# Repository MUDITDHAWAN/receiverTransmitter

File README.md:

# receiverTransmitter

Components Type Purpose
    HC-49U Crystal Oscillator: Generate 2MHz signal
    CD4017BE Frequency Divider:  Convert 2MHz signal to 40KHz signal
    CD4049 Buffer Amplifier:  Allows for impedance transformation and protects
        circuits from fluctuations in currents.
    MCUSD16A40S12R0 Piezoelectric Transducer: Convert electrical to ultrasonic signal and back
        (Transmitter and Receiver)
    MC33079 Low Noise Amplifier: Amplify received signal without introducing too much
        noise

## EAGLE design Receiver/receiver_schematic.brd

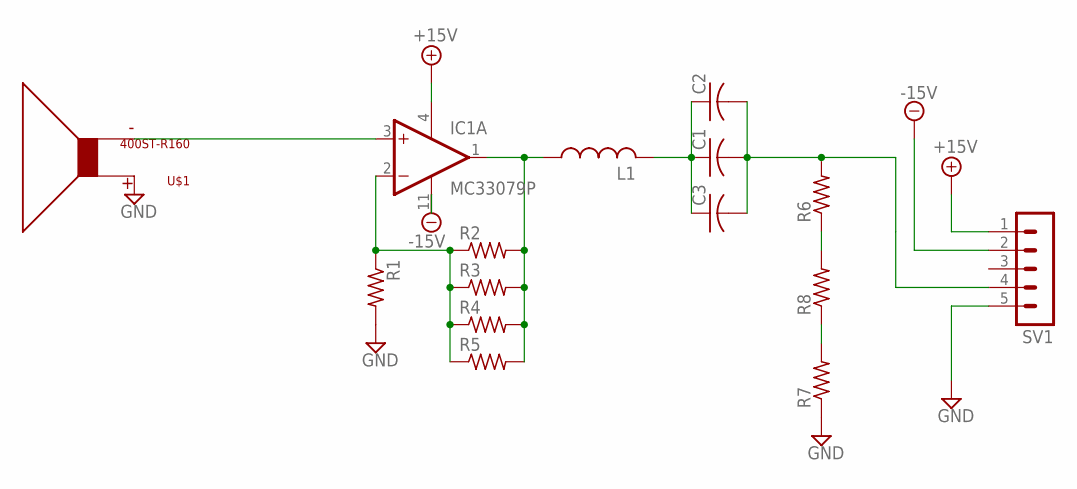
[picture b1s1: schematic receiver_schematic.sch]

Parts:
C1, C2, C3: C-US025-030X050; C025-030X050
IC1: MC33079P; DIL14
L1: L-US0204/5; 0204/5
R1, R2, R3, R4, R5, R6, R7, R8: R-US_0204/5; 0204/5
SV1: MA05-1
U$1: 400ST-R160; 400STR160

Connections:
+15V: IC1.4 (V+), SV1.1
-15V: IC1.11 (V-), SV1.2
GND: R1.2, R7.1, SV1.5, U$1.P$1
unnamed: IC1.3 (+IN), U$1.P$2
unnamed: C1.1, C2.1, C3.1, L1.2
unnamed: IC1.1 (OUT), L1.1, R2.2, R3.2, R4.2, R5.2
unnamed: IC1.2 (-IN), R1.1, R2.1, R3.1, R4.1, R5.1
unnamed: C1.2, C2.2, C3.2, R6.2, SV1.4
unnamed: R6.1, R8.2
unnamed: R7.2, R8.1

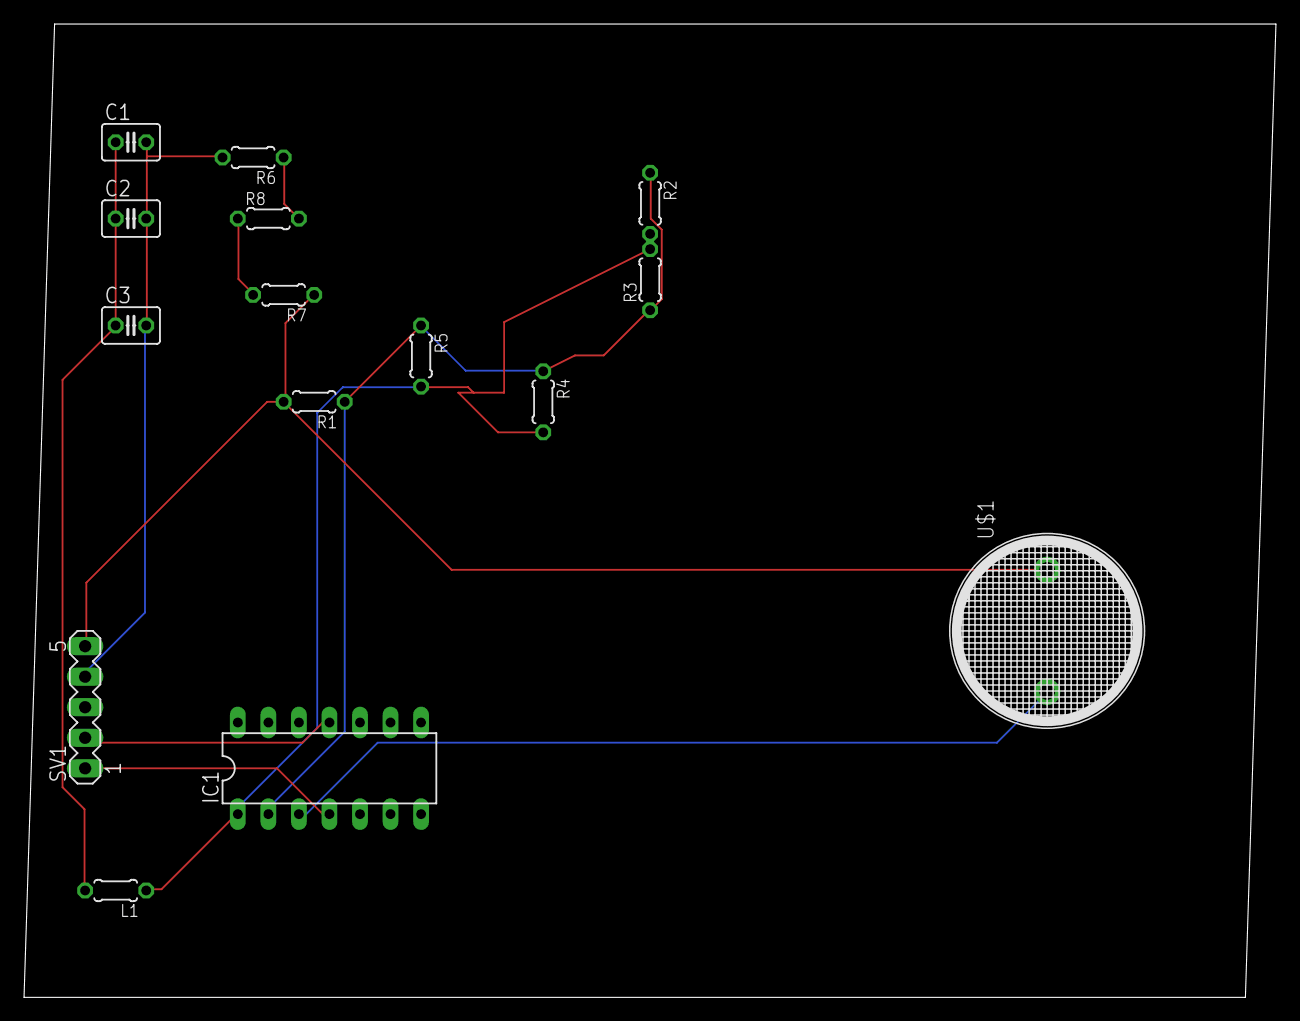
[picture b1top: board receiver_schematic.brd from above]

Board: 2 copper layers, 104.1 x 81.0 mm, 15 parts (0 on the bottom side), 10 nets.

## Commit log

2020-01-10 Added receiver .brd and .sch; transmitter cam outputs
2020-01-11 Components used
